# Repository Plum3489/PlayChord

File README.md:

# PlayChord - XIAO RP2040 MIDI Chord Controller
PlayChord is a USB MIDI chord controller built around the Seeed XIAO RP2040 microcontroller. It allows musicians and producers to play full chords with a single button press :]

### Key Features
- **7 Chord Buttons** - Play diatonic chords (I, ii, iii, IV, V, vi, vii°) in any key
- **Rotary Encoder** - Switch between 12 musical keys (C through B)
- **Chord Type Selection** - Toggle between Triads (3-note), 7th chords, and 9th chords
- **Octave Control** - Shift the entire chord range up/down by +-2 octaves
- **Major/Minor Mode** - Switch between Major and Natural Minor scales
- **OLED Display** - Display of current key, mode, and settings
- **USB MIDI** - Direct USB-C connection to DAW/music software

## Hardware Specification

### Bill of Materials (BOM)
| Qty | Item | Notes | Unit Price (USD) | Subtotal (USD) |
|----:|------|-------|-----------------:|---------------:|
| 1 | PCB (unsoldered) | PCB 1 | $5.00 | $5.00 |
| 1 | Seeed XIAO RP2040 | | $5.00 | $5.00 |
| 12 | Through-hole 1N4148 Diodes | | $0.03 | $0.36 |
| 11 | MX-Style switches | | $0.30 | $3.30 |
| 1 | EC11 Rotary Encoder | | $1.50 | $1.50 |
| 1 | 0.91" OLED Display | Pin order: **GND-VCC-SCL-SDA** (PCB must match) | $2.50 | $2.50 |
| 11 | White Blank DSA Keycaps | | $0.25 | $2.75 |
| 3 | M3×16 mm Screws | | $0.10 | $0.30 |
| 3 | M3×5×4 mm Heat-set Inserts | | $0.15 | $0.45 |
| | **Total** | | | **$21.16** |

### PCB Specifications
PCB Dimensions: 80mm × 91.835mm
Layer Count: 2 

### Case Specifications
Outer Dimensions: 100mm × 111.84mm × 16.9mm

## Software Architecture

### Stack

- **Framework:** Arduino (PlatformIO compatible)
- **USB Communication:** Adafruit TinyUSB Library (MIDI over USB)
- **Display Driver:** Adafruit SSD1306 (I2C)
- **MIDI Library:** fortyseveneffects/MIDI Library v5.0.2

### How it works ^^

#### 1. **Matrix Scanning** (`scanMatrix()`)

Purpose: Read button states from 3×4 switch matrix
Method:  Row-by-row activation with column polling
Timing:  Scanned every 5ms in main loop

Process:
1. Set Row pin to LOW (activate)
2. Read all 4 Column pins (INPUT_PULLUP)
3. Debounce each switch (50ms delay)
4. Trigger press/release events
5. Set Row pin to HIGH (deactivate)
6. Move to next row

Rotary Encoder
Purpose: Change musical key via rotary encoder
Method:  Hardware interrupt on encoder Pin A
Timing:  Interrupt-driven (no polling)

Process:
1. Encoder Pin A triggers FALLING interrupt
2. Read Pin B to determine direction
3. Increment/Decrement encoderPos
4. Debounce: Ignore interrupts < 5ms apart
5. In main loop: Convert position delta to key change
6. Wrap around between C (0) and B (11)

Yeah!

##Chord Gen!!
Purpose: Convert button press -> MIDI note-on events
Input:   Chord index (0-6, representing I through vii°)

Process:
1. Select chord table (MAJOR_TRIADS or MINOR_TRIADS)
2. Calculate 3 base notes:
   - note = BASE_OCTAVE + currentKey + interval + (octaveShift × 12)
   - BASE_OCTAVE = 60 (C4 = middle C in MIDI)
   - currentKey = 0-11 (semitone offset)
   - interval = chord tone (0, 4, 7 for C Major triad)
   - octaveShift = -2 to +2 (user-controlled)
3. Send MIDI Note-On (velocity=100) for each note
4. Track active notes in activeNotes[128] array
5. If chordType ≥ 1: Add 7th tone
6. If chordType = 2: Add 9th tone

##Button functionality 
Button	    Mode	    Action
------------------------------
SW1-7	    Any	        Play diatonic chord I-vii°
SW8	    Release	     Octave shift +1 (max +2)
SW9	    Press	     Toggle chord type: Triad → 7th → 9th
SW10	    Release	     Octave shift -1 (min -2)
SW11	    Release      Toggle Major ↔ Minor mode
SW12	    Press	     PANIC: All notes off

# Flashing with PlatformIO
1. Open project folder in VS Code
2. Click PlatformIO Home icon (alien head)
3. Click "Open Project"
4. Select your project folder
5. Verify board is set to: seeed_xiao_rp2040
6. Connect XIAO RP2040 via USB-C
7. Click: PlatformIO -> Upload
8. Wait for "Upload successful"

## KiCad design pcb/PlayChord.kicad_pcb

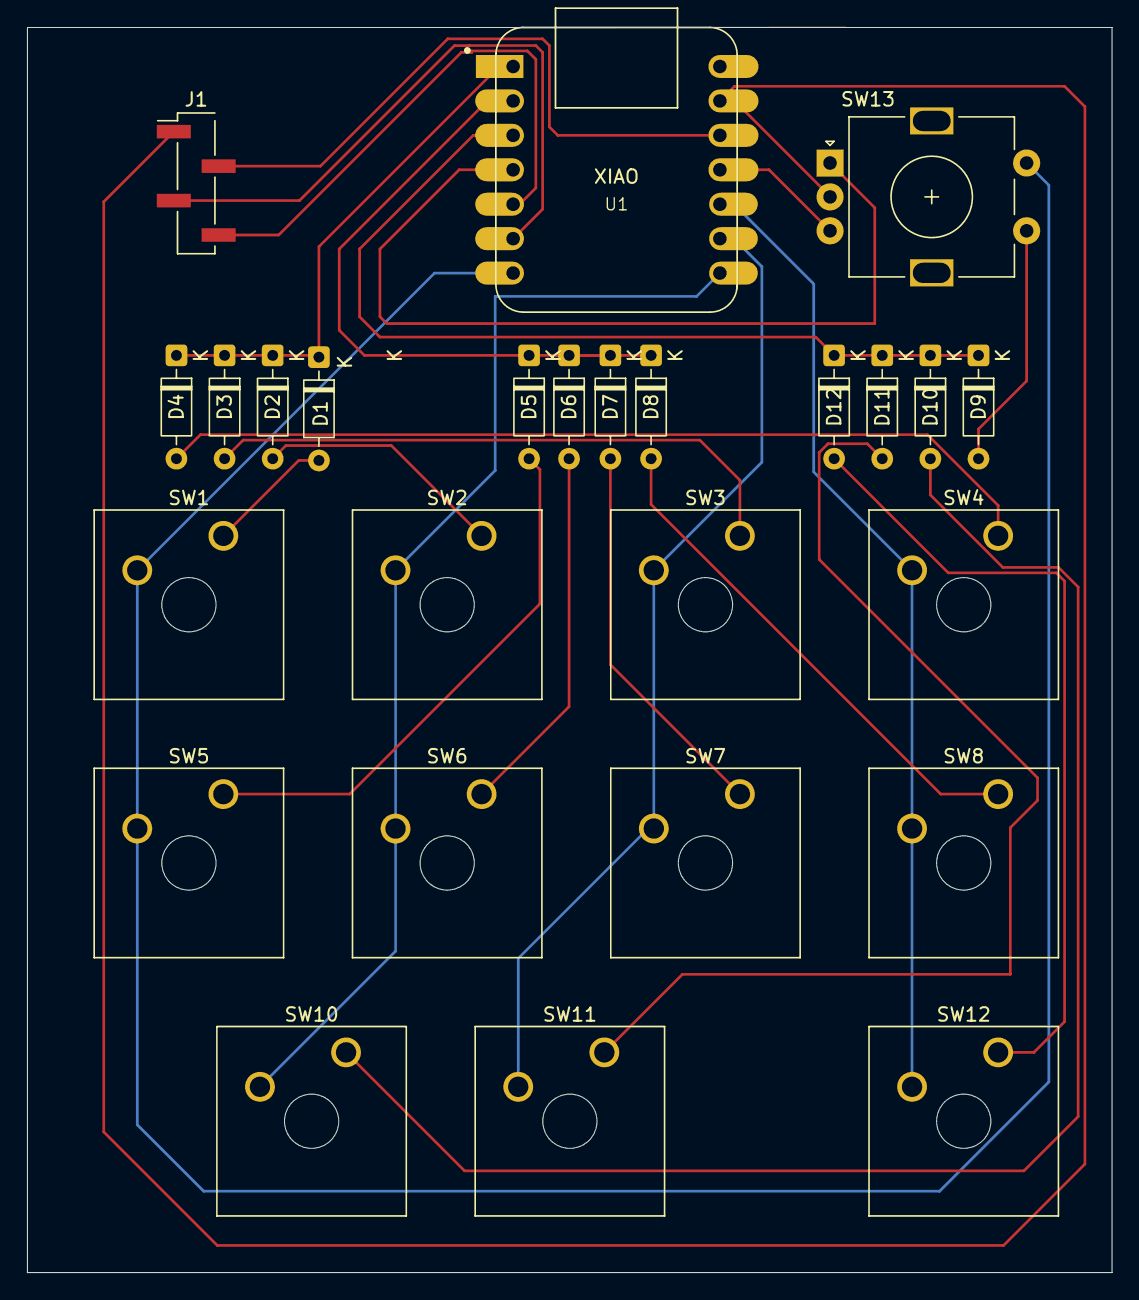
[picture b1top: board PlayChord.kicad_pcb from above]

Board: 2 copper layers, 80.0 x 91.8 mm, 26 parts (0 on the bottom side), 25 nets.

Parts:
D1, D2, D3, D4, D5, D6, D7, D8, D9, D10, D11, D12: D_DO-35_SOD27_P7.62mm_Horizontal
J1: Conn_01x04_Pin; PinHeader_1x04_P2.54mm_Vertical_SMD_Pin1Left
SW1: I; SW_Cherry_MX_1.00u_Plate
SW2: II; SW_Cherry_MX_1.00u_Plate
SW3: III; SW_Cherry_MX_1.00u_Plate
SW4: IV; SW_Cherry_MX_1.00u_Plate
SW5: V; SW_Cherry_MX_1.00u_Plate
SW6: VI; SW_Cherry_MX_1.00u_Plate
SW7: VII; SW_Cherry_MX_1.00u_Plate
SW8: UP; SW_Cherry_MX_1.00u_Plate
SW10, SW11: SW_Cherry_MX_1.00u_Plate
SW12: DOWN; SW_Cherry_MX_1.00u_Plate
SW13: RotaryEncoder_Switch; RotaryEncoder_Alps_EC11E-Switch_Vertical_H20mm
U1: MOUDLE-SEEEDUINO-XIAO; XIAO-Generic-Hybrid-14P-2.54-21X17.8MM

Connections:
unnamed: D1.2 (A), SW1.1
unnamed: D1.1 (K), D2.1 (K), D3.1 (K), D4.1 (K), U1.1 (PA02_A0_D0)
unnamed: D2.2 (A), SW2.1
unnamed: D3.2 (A), SW3.1
unnamed: D4.2 (A), SW4.1
unnamed: D5.2 (A), SW5.1
unnamed: D5.1 (K), D6.1 (K), D7.1 (K), D8.1 (K), U1.2 (PA4_A1_D1)
unnamed: D6.2 (A), SW6.1
unnamed: D7.2 (A), SW7.1
unnamed: D8.2 (A), SW8.1
unnamed: D9.2 (A), SW13.S1
unnamed: D10.2 (A), SW10.1
unnamed: D9.1 (K), D10.1 (K), D11.1 (K), D12.1 (K), U1.3 (PA10_A2_D2)
unnamed: D11.2 (A), SW11.1
unnamed: D12.2 (A), SW12.1
unnamed: J1.1, SW13.C, U1.13 (GND)
unnamed: J1.2, U1.12 (3V3)
unnamed: J1.3, U1.6 (PA9_A5_D5_SCL)
unnamed: J1.4, U1.5 (PA8_A4_D4_SDA)
unnamed: SW4.2, SW8.2, SW12.2, U1.10 (PA5_A9_D9_MISO)
unnamed: SW13.B, U1.11 (PA6_A10_D10_MOSI)
unnamed: SW3.2, SW7.2, SW11.2, U1.9 (PA7_A8_D8_SCK)
unnamed: SW13.A, U1.4 (PA11_A3_D3)
unnamed: SW1.2, SW5.2, SW13.S2, U1.7 (PB08_A6_D6_TX)
unnamed: SW2.2, SW6.2, SW10.2, U1.8 (PB09_A7_D7_RX)
